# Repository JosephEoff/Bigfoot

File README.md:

# Bigfoot
Bigfoot is a sewing machine motor speed control made to truly control the speed rather than merely regulating the power.

|Bigfoot and an Adler class 8 sewing machine|
|------------------------------------------|
||

It uses feedback through a tachometer and a PID controller to maintain the speed set by the foot pedal.  A sewing machine with a Bigfoot controller can steadily work its way through thick stacked leather - provided you are using a solid old vintage sewing machine.

[More details of the background and development of Bigfoot can be found in this series of posts on my blog.](https://josepheoff.github.io/posts/motorcontrol-toc)

Here's Bigfoot and the Adler working through eight, then two, then four layers of fake leather while maintaining a steady speed:

https://github.com/JosephEoff/Bigfoot/assets/13119635/e1ab42f6-7f08-4af5-ab49-b018099e2578

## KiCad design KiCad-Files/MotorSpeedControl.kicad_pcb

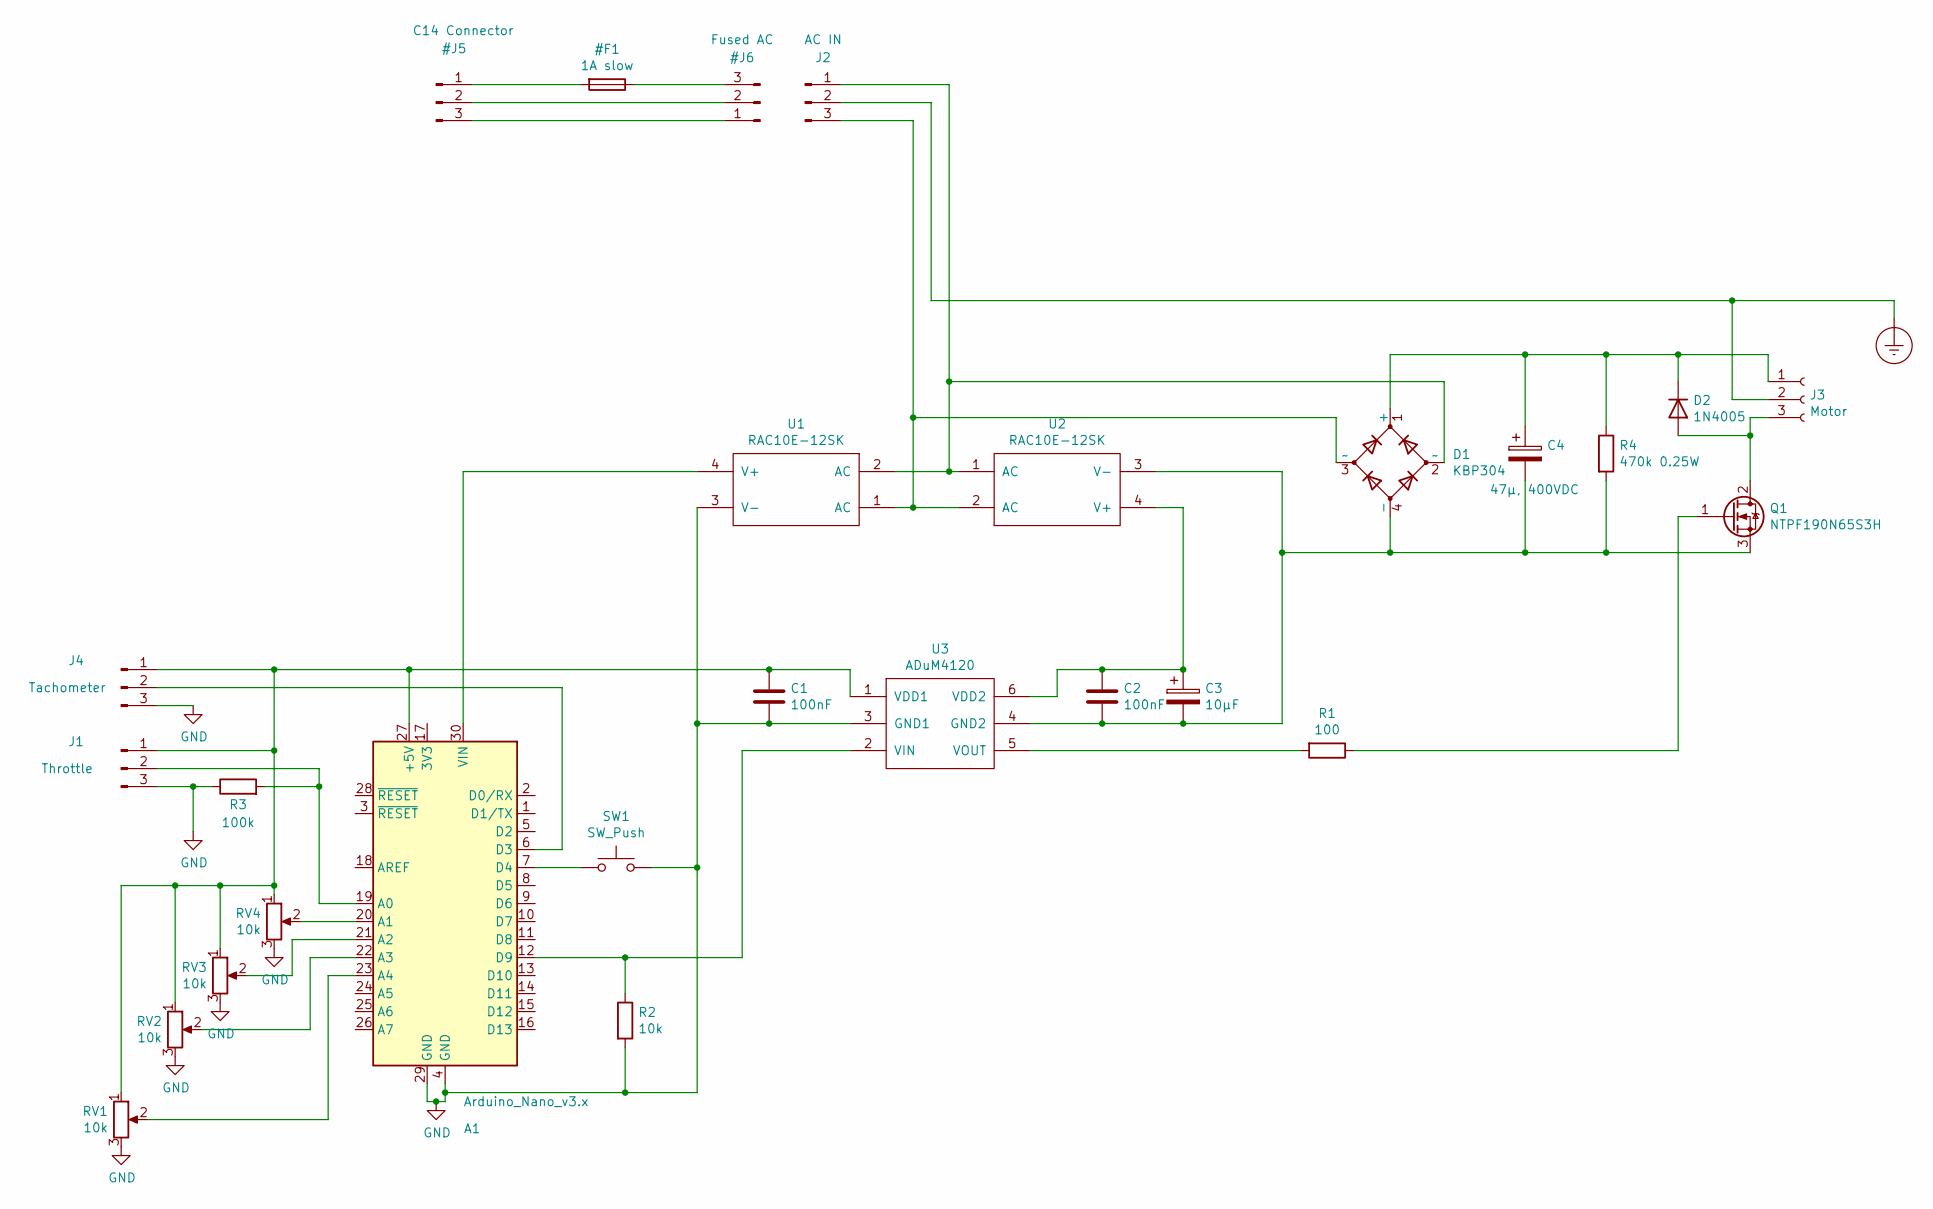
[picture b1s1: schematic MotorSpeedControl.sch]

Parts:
A1: Arduino_Nano_v3.x; Arduino_Nano
C1, C2: 100nF; C_0805
C3: 10µF; CP_Radial_D5.0mm_P2.50mm
C4: 47µ, 400VDC; CP_Radial_D18.0mm_P7.50mm
D1: KBP304; KBP
D2: 1N4005; D_DO-41_SOD81_P12.70mm_Horizontal
J1: Throttle; Pin_Header_Straight_1x03_Pitch2.54mm
J2: AC IN; TerminalBlock_bornier-3_P5.08mm
J3: Motor; TerminalBlock_bornier-3_P5.08mm
J4: Tachometer; Pin_Header_Straight_1x03_Pitch2.54mm
Q1: NTPF190N65S3H; TO-220-3_Vertical
R1: 100; R_1206
R2: 10k; R_0805
R3: 100k; R_0805
R4: 470k 0.25W; R_Axial_DIN0207_L6.3mm_D2.5mm_P7.62mm_Horizontal
RV1, RV2, RV3, RV4: 10k; Potentiometer_Trimmer_Bourns_3339W_Vertical
SW1: SW_Push; SW_TH_Tactile_Omron_B3F-10xx
U1, U2: RAC10E-12SK; RAC10E
U3: ADuM4120; SOIC-IC6

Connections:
Earth_Protective: J2.2, J3.2
GND: A1.4 (GND), A1.29 (GND), C1.2, J1.3, J4.3, R2.2, R3.1, RV1.3, RV2.3, RV3.3, RV4.3, SW1.2, U1.3 (V-), U3.3 (GND1)
unnamed: A1.6 (D3), J4.2
unnamed: A1.7 (D4), SW1.1
unnamed: A1.12 (D9), R2.1, U3.2 (VIN)
unnamed: A1.19 (A0), J1.2, R3.2
unnamed: A1.20 (A1), RV4.2
unnamed: A1.21 (A2), RV3.2
unnamed: A1.22 (A3), RV2.2
unnamed: A1.23 (A4), RV1.2
unnamed: A1.27 (+5V), C1.1, J1.1, J4.1, RV1.1, RV2.1, RV3.1, RV4.1, U3.1 (VDD1)
unnamed: A1.30 (VIN), U1.4 (V+)
unnamed: C2.1, C3.1, U2.4 (V+), U3.6 (VDD2)
unnamed: C2.2, C3.2, C4.2, D1.4 (-), Q1.3 (S), R4.2, U2.3 (V-), U3.4 (GND2)
unnamed: C4.1, D1.1 (+), D2.1 (K), J3.1, R4.1
unnamed: D1.2 (~~), J2.1, U1.2 (AC), U2.1 (AC)
unnamed: D1.3 (~~), J2.3, U1.1 (AC), U2.2 (AC)
unnamed: D2.2 (A), J3.3, Q1.2 (D)
unnamed: Q1.1 (G), R1.1
unnamed: R1.2, U3.5 (VOUT)

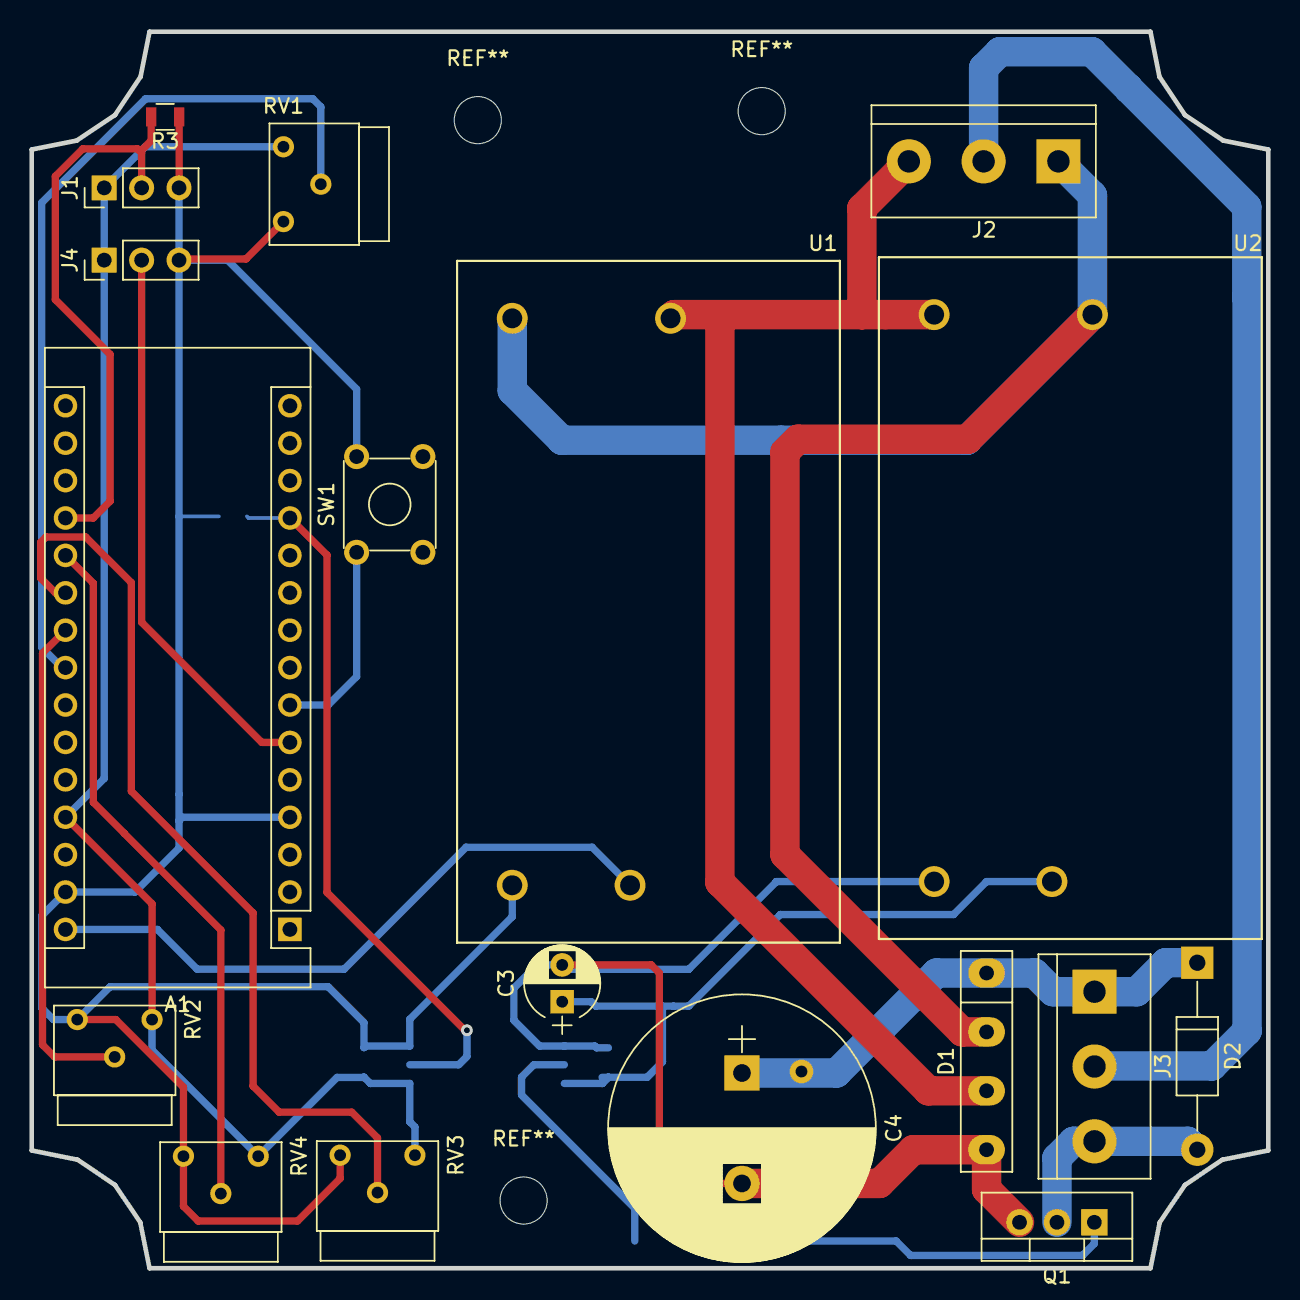
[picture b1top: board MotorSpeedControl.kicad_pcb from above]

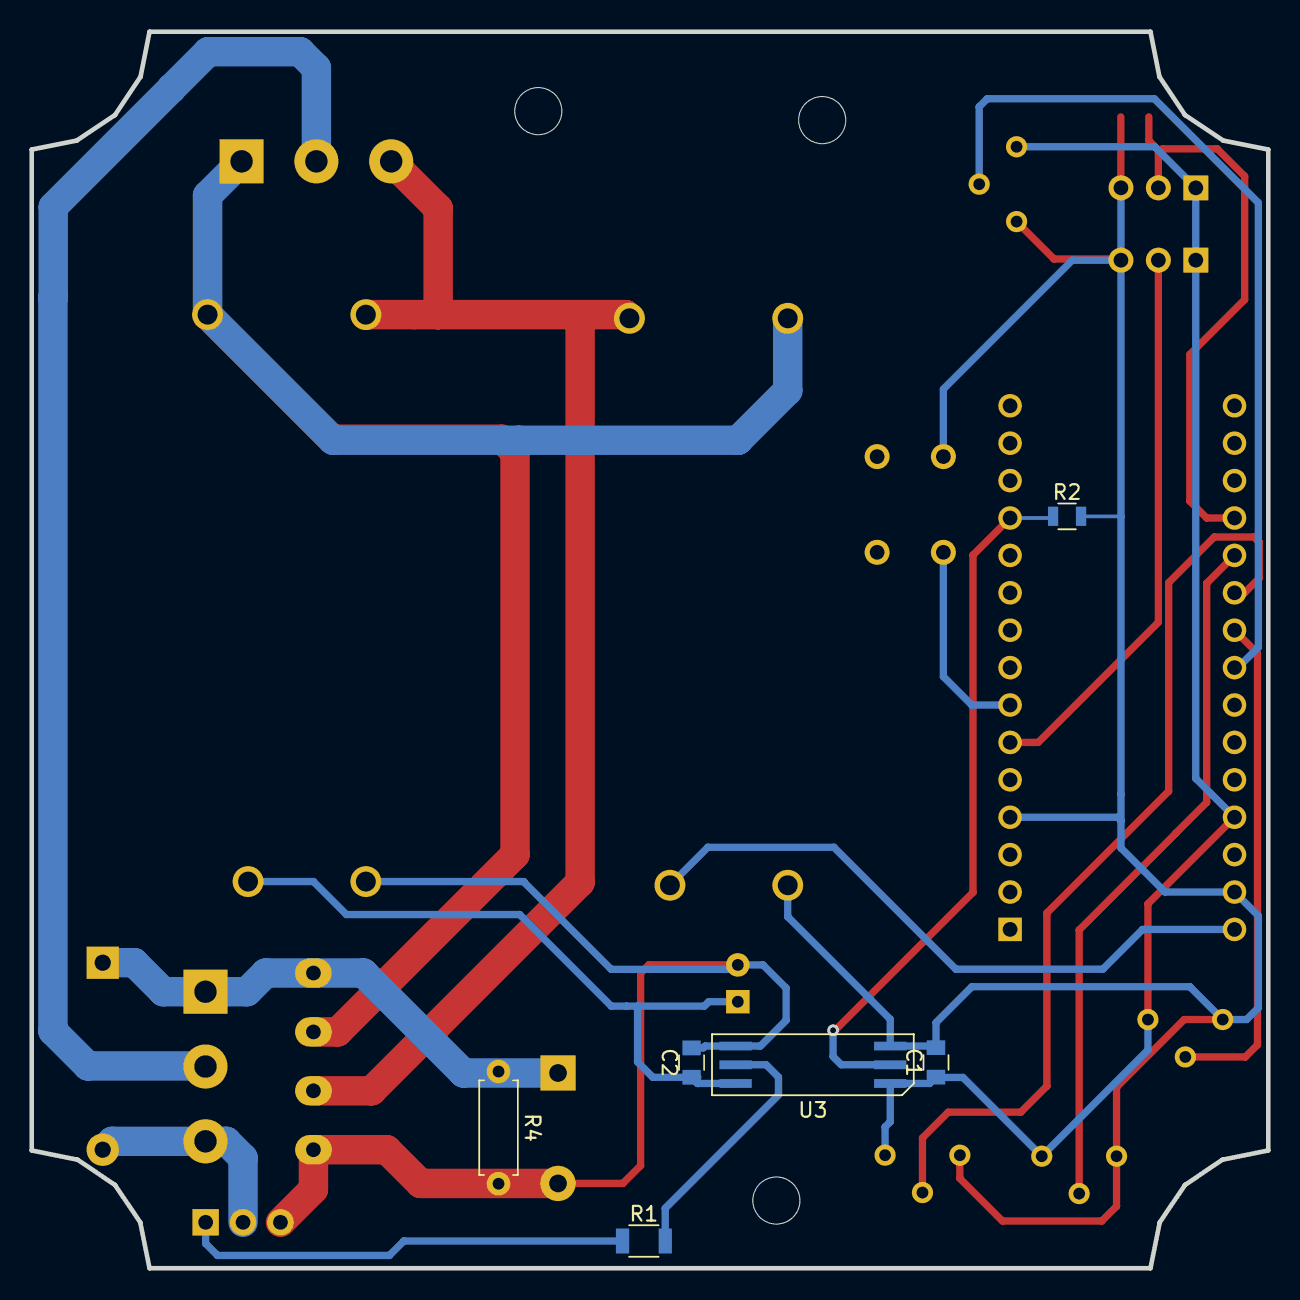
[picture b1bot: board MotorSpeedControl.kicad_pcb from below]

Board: 2 copper layers, 84.0 x 84.0 mm, 24 parts (6 on the bottom side), 20 nets.

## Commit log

2023-11-11 Initial commit. Still a mess.
2023-11-11 A little bit of cleanup.
2023-11-12 Updated schematic.
2023-11-12 Added tachometer info.
